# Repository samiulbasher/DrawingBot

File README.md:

# DrawingBot
Drawing Bot is a CNC plotter machine.

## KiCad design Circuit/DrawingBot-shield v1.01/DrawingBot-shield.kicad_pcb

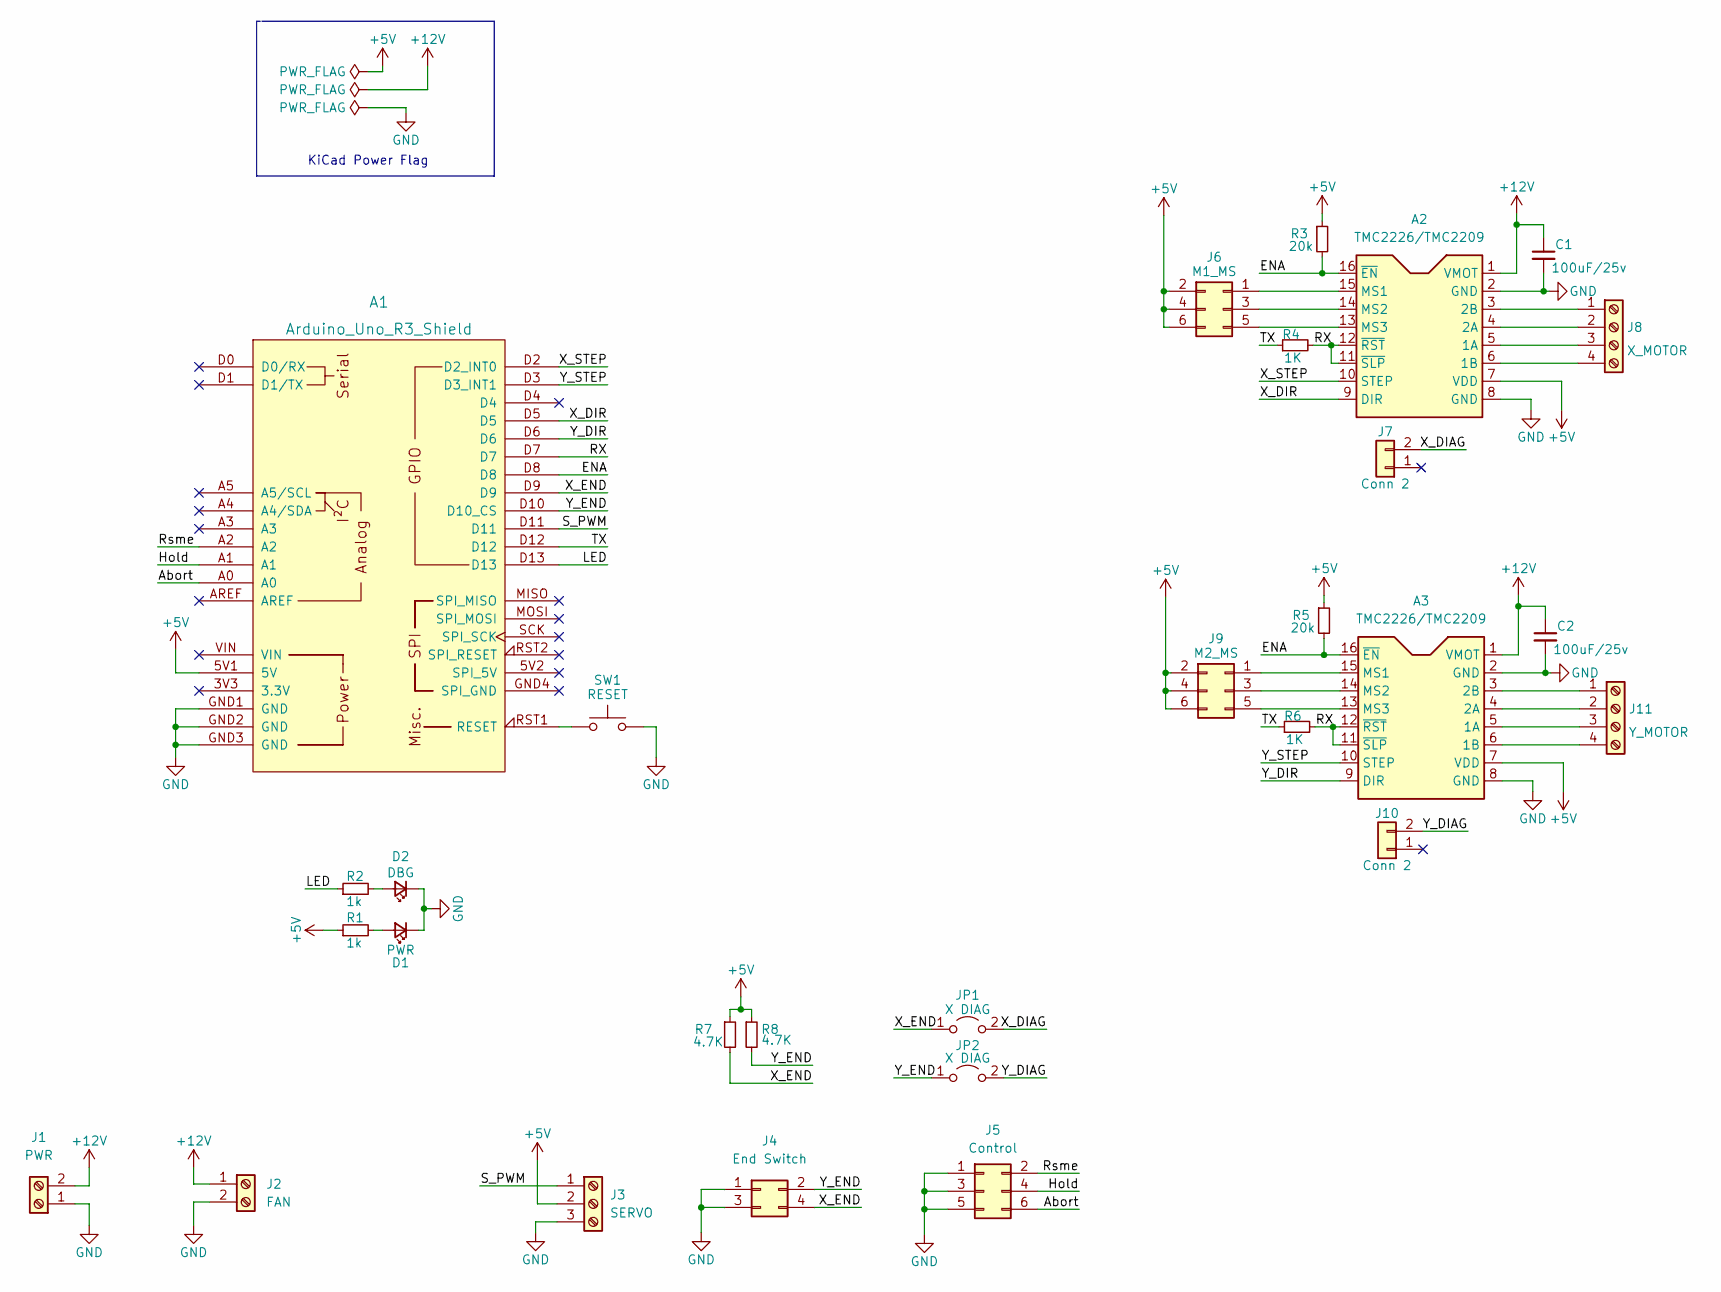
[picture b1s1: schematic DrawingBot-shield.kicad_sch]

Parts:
A1: Arduino_Uno_R3_Shield; Arduino_Uno_Socket
A2, A3: TMC2226/TMC2209; Pololu_Breakout
C1, C2: 100uF/25v; CP_Radial_D5.0mm_P2.00mm
D1: PWR; LED_D3.0mm
D2: DBG; LED_D3.0mm
J1: PWR; TerminalBlock_Phoenix_PT-1,5-2-5.0-H_1x02_P5.00mm_Horizontal
J2: FAN; Molex_KK-254_AE-6410-02A_1x02_P2.54mm_Vertical
J3: SERVO; Molex_KK-254_AE-6410-03A_1x03_P2.54mm_Vertical
J4: End Switch; PinHeader_2x02_P2.54mm_Vertical
J5: Control; PinHeader_2x03_P2.54mm_Vertical
J6: M1_MS; PinHeader_2x03_P2.54mm_Vertical
J7, J10: Conn 2; PinHeader_1x02_P2.54mm_Vertical
J8: X_MOTOR; Molex_KK-254_AE-6410-04A_1x04_P2.54mm_Vertical
J9: M2_MS; PinHeader_2x03_P2.54mm_Vertical
J11: Y_MOTOR; Molex_KK-254_AE-6410-04A_1x04_P2.54mm_Vertical
JP1, JP2: X DIAG; SolderJumper-2_P1.3mm_Open_RoundedPad1.0x1.5mm
R1, R2: 1k; R_Axial_DIN0204_L3.6mm_D1.6mm_P7.62mm_Horizontal
R3, R5: 20k; R_Axial_DIN0204_L3.6mm_D1.6mm_P7.62mm_Horizontal
R4, R6: 1K; R_Axial_DIN0204_L3.6mm_D1.6mm_P7.62mm_Horizontal; JLCPCB Part C21190
R7, R8: 4.7K; R_Axial_DIN0204_L3.6mm_D1.6mm_P7.62mm_Horizontal
SW1: RESET; SW_PUSH_6mm_H4.3mm; JLCPCB Part C318884

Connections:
+5V: A1.5V1 (5V), A2.7 (VDD), A3.7 (VDD), J3.2, J6.2, J6.4, J6.6, J9.2, J9.4, J9.6, R1.1, R3.1, R5.1, R7.1, R8.1
+12V: A2.1 (VMOT), A3.1 (VMOT), C1.1, C2.1, J1.2, J2.1
/Abort: A1.A0, J5.6
/ENA: A1.D8, A2.16 (~EN), A3.16 (~EN), R3.2, R5.2
/Hold: A1.A1, J5.4
/LED: A1.D13, R2.1
/RX: A1.D7, A2.11 (~SLP), A2.12 (~RST), A3.11 (~SLP), A3.12 (~RST), R4.2, R6.2
/Rsme: A1.A2, J5.2
/S_PWM: A1.D11, J3.1
/TX: A1.D12, R4.1, R6.1
/X_DIAG: J7.2, JP1.2 (B)
/X_DIR: A1.D5, A2.9 (DIR)
/X_END: A1.D9, J4.4, JP1.1 (A), R7.2
/X_STEP: A1.D2 (D2_INT0), A2.10 (STEP)
/Y_DIAG: J10.2, JP2.2 (B)
/Y_DIR: A1.D6, A3.9 (DIR)
/Y_END: A1.D10 (D10_CS), J4.2, JP2.1 (A), R8.2
/Y_STEP: A1.D3 (D3_INT1), A3.10 (STEP)
GND: A1.GND1 (GND), A1.GND2 (GND), A1.GND3 (GND), A2.2 (GND), A2.8 (GND), A3.2 (GND), A3.8 (GND), C1.2, C2.2, D1.1 (K), D2.1 (K), J1.1, J2.2, J3.3, J4.1, J4.3, J5.1, J5.3, J5.5, SW1.2
unnamed: A1.RST1 (RESET), SW1.1
unnamed: A2.3 (2B), J8.1
unnamed: A2.4 (2A), J8.2
unnamed: A2.5 (1A), J8.3
unnamed: A2.6 (1B), J8.4
unnamed: A2.13 (MS3), J6.5
unnamed: A2.14 (MS2), J6.3
unnamed: A2.15 (MS1), J6.1
unnamed: A3.3 (2B), J11.1
unnamed: A3.4 (2A), J11.2
unnamed: A3.5 (1A), J11.3
unnamed: A3.6 (1B), J11.4
unnamed: A3.13 (MS3), J9.5
unnamed: A3.14 (MS2), J9.3
unnamed: A3.15 (MS1), J9.1
unnamed: D1.2 (A), R1.2
unnamed: D2.2 (A), R2.2

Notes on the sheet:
KiCad Power Flag

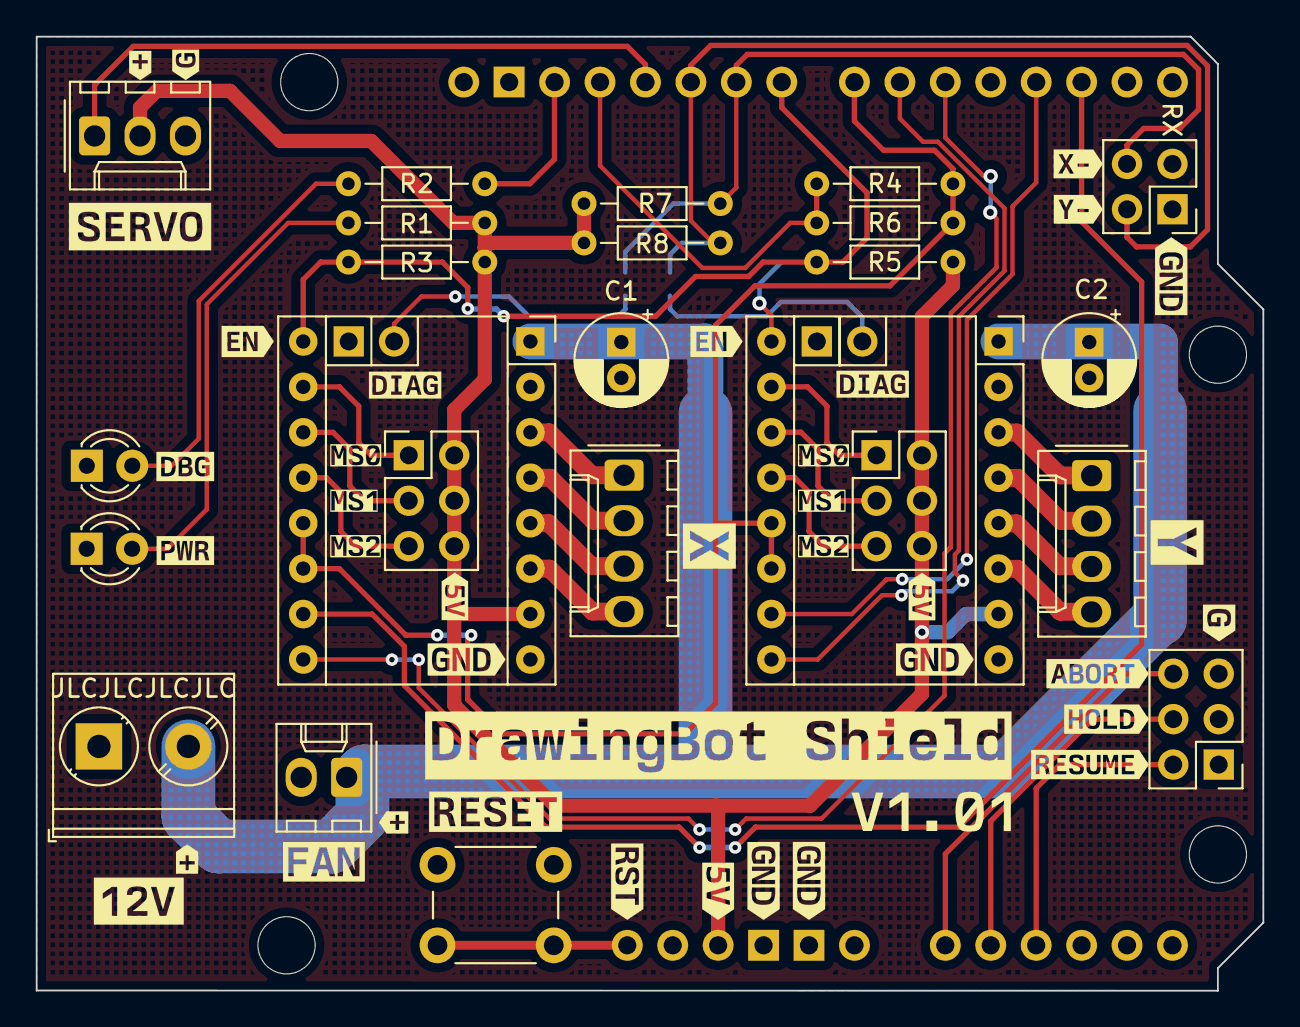
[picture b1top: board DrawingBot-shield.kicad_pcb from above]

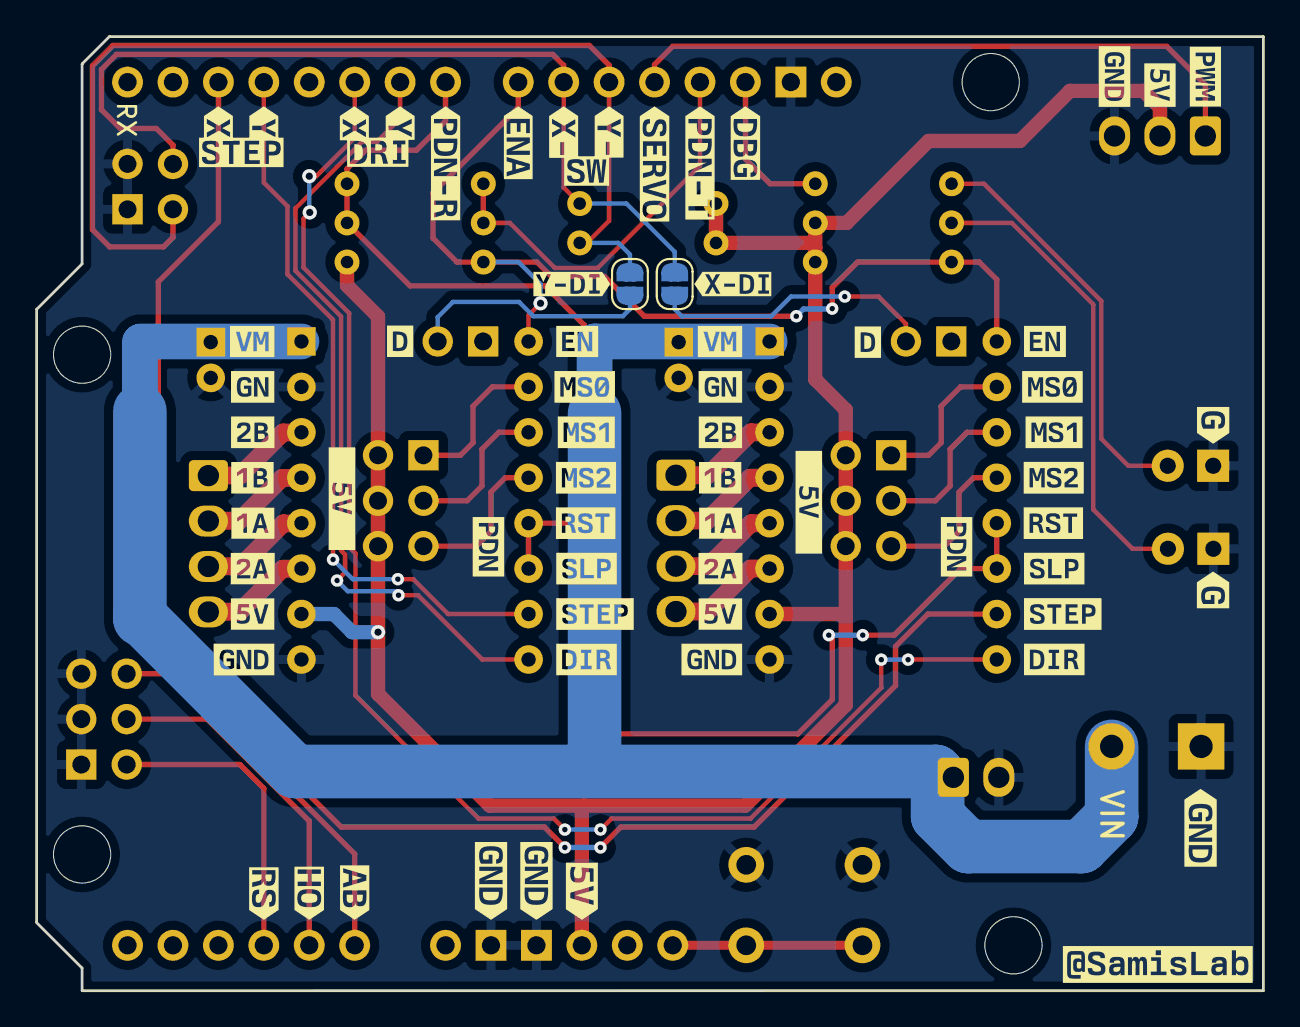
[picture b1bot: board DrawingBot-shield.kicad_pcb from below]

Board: 2 copper layers, 68.6 x 53.3 mm, 135 parts (69 on the bottom side), 36 nets.

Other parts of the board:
kibuzzard-65A4F46A, kibuzzard-65A4F46A#2: G***; kibuzzard-65A4F46A
kibuzzard-65A4FB8D: G***; kibuzzard-65A4FB8D
kibuzzard-65E6A4A7, kibuzzard-65E6A4A7#2: G***; kibuzzard-65E6A4A7
kibuzzard-65E6A4BF, kibuzzard-65E6A4BF#2: G***; kibuzzard-65E6A4BF
kibuzzard-65E6A15C: G***; kibuzzard-65E6A15C
kibuzzard-65E6A016: G***; kibuzzard-65E6A016
kibuzzard-65E6A22A, kibuzzard-65E6A22A#2: G***; kibuzzard-65E6A22A
kibuzzard-65E6A22F, kibuzzard-65E6A22F#2: G***; kibuzzard-65E6A22F
kibuzzard-65E6A48D: G***; kibuzzard-65E6A48D
kibuzzard-65E6A50A: G***; kibuzzard-65E6A50A
kibuzzard-65E6A52D: G***; kibuzzard-65E6A52D
kibuzzard-65E6A239, kibuzzard-65E6A239#2: G***; kibuzzard-65E6A239
kibuzzard-65E6A498, kibuzzard-65E6A498#2: G***; kibuzzard-65E6A498
kibuzzard-65E6A521: G***; kibuzzard-65E6A521
kibuzzard-65E6A533: G***; kibuzzard-65E6A533
kibuzzard-65E6AFEA: G***; kibuzzard-65E6AFEA
kibuzzard-65E68A9D: G***; kibuzzard-65E68A9D
kibuzzard-65E68A83: G***; kibuzzard-65E68A83
kibuzzard-65E68AE8: G***; kibuzzard-65E68AE8
kibuzzard-65E68D6E, kibuzzard-65E68D6E#2: G***; kibuzzard-65E68D6E
kibuzzard-65E68D88, kibuzzard-65E68D88#2: G***; kibuzzard-65E68D88
kibuzzard-65E68E4B, kibuzzard-65E68E4B#2: G***; kibuzzard-65E68E4B
kibuzzard-65E68E7D, kibuzzard-65E68E7D#2: G***; kibuzzard-65E68E7D
kibuzzard-65E68EA2, kibuzzard-65E68EA2#2: G***; kibuzzard-65E68EA2
kibuzzard-65E68ECB, kibuzzard-65E68ECB#2: G***; kibuzzard-65E68ECB
kibuzzard-65E68EEA, kibuzzard-65E68EEA#2, kibuzzard-65E68EEA#3: G***; kibuzzard-65E68EEA
kibuzzard-65E68EF2, kibuzzard-65E68EF2#2, kibuzzard-65E68EF2#3: G***; kibuzzard-65E68EF2
kibuzzard-65E68F9E, kibuzzard-65E68F9E#2: G***; kibuzzard-65E68F9E
kibuzzard-65E68F92, kibuzzard-65E68F92#2: G***; kibuzzard-65E68F92
kibuzzard-65E68F98, kibuzzard-65E68F98#2: G***; kibuzzard-65E68F98
kibuzzard-65E69A04: G***; kibuzzard-65E69A04
kibuzzard-65E69DAF: G***; kibuzzard-65E69DAF
kibuzzard-65E69E92: G***; kibuzzard-65E69E92
kibuzzard-65E69ED1: G***; kibuzzard-65E69ED1
kibuzzard-65E687F6: G***; kibuzzard-65E687F6
kibuzzard-65E688B8: G***; kibuzzard-65E688B8
kibuzzard-65E689B2: G***; kibuzzard-65E689B2
kibuzzard-65E689EF, kibuzzard-65E689EF#2: G***; kibuzzard-65E689EF
kibuzzard-65E698B6: G***; kibuzzard-65E698B6
kibuzzard-65E698DF: G***; kibuzzard-65E698DF
kibuzzard-65E699B0: G***; kibuzzard-65E699B0
kibuzzard-65E699B6: G***; kibuzzard-65E699B6
kibuzzard-65E699CF: G***; kibuzzard-65E699CF
kibuzzard-65E6858D, kibuzzard-65E6858D#2: G***; kibuzzard-65E6858D
kibuzzard-65E6974F: G***; kibuzzard-65E6974F
kibuzzard-65E6976E: G***; kibuzzard-65E6976E
kibuzzard-65E6977A: G***; kibuzzard-65E6977A
kibuzzard-65E6994C: G***; kibuzzard-65E6994C
kibuzzard-65E6996A: G***; kibuzzard-65E6996A
kibuzzard-65E68518, kibuzzard-65E68518#2: G***; kibuzzard-65E68518
kibuzzard-65E68692, kibuzzard-65E68692#2: G***; kibuzzard-65E68692
kibuzzard-65E68953: G***; kibuzzard-65E68953
kibuzzard-65E68994: G***; kibuzzard-65E68994
kibuzzard-65E69043, kibuzzard-65E69043#2: G***; kibuzzard-65E69043
kibuzzard-65E69079, kibuzzard-65E69079#2: G***; kibuzzard-65E69079
kibuzzard-65E69089, kibuzzard-65E69089#2: G***; kibuzzard-65E69089
kibuzzard-65E69758: G***; kibuzzard-65E69758
kibuzzard-65E69760: G***; kibuzzard-65E69760
kibuzzard-65E69767: G***; kibuzzard-65E69767
kibuzzard-65E69775: G***; kibuzzard-65E69775
kibuzzard-65E69903, kibuzzard-65E69903#2: G***; kibuzzard-65E69903
kibuzzard-65E69945: G***; kibuzzard-65E69945
kibuzzard-651A1A52: G***; kibuzzard-651A1A52
kibuzzard-6513B43E: G***; kibuzzard-6513B43E
kibuzzard-6514EA0E, kibuzzard-6514EA0E#2, kibuzzard-6514EA0E#3: G***; kibuzzard-6514EA0E
kibuzzard-6646A0B8, kibuzzard-6646A0B8#2: G***; kibuzzard-6646A0B8
kibuzzard-6646A056, kibuzzard-6646A056#2: G***; kibuzzard-6646A056
kibuzzard-6646BEC2: G***; kibuzzard-6646BEC2
kibuzzard-6646C4C5: G***; kibuzzard-6646C4C5
kibuzzard-6646C040: G***; kibuzzard-6646C040
kibuzzard-6646C366: G***; kibuzzard-6646C366
kibuzzard-6646C738: G***; kibuzzard-6646C738
kibuzzard-6646C756: G***; kibuzzard-6646C756
kibuzzard-66469F7A: G***; kibuzzard-66469F7A

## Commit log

2024-03-03 Create Firmware
2024-03-03 Update Firmware
2024-03-03 filename
2024-03-08 add 360 servo support
2024-03-31 add DrawingBot Shield
2024-05-17 upload circuit
2024-05-27 update config
2024-06-06 upload 3D model
